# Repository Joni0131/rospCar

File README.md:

- [rospCar](#rospcar)
- [Work progression](#work-progression)
  - [1. Old System](#1-old-system)
  - [2. Planning](#2-planning)
  - [3. ESP-32](#3-esp-32)
  - [4. Brain](#4-brain)
- [Resume](#resume)

# rospCar

This repository contains the whole redevelopment of an old RC car.

To change the control system to an esp32 and a ROS communication with the computer to potentially implement a SLAM algorithm.

# Work progression

I structured my work in the following four steps. Those are shortly discussed on this page for more detailed information on each step please correspond to each designated page.

## 1. [Old System](oldSystem/)

The first step of the redevelopment process consists of understanding and checking the currently used electronics. As well as their functionality.

## 2. [Planning](upgradePlan/)

In the second phase, I chose the requirements for the new car, ordered parts that fulfill those requirements as well as designed the new circuit diagram.

## 3. [ESP-32](esp/)

The third step is considered the heart of the hardware development process. Here I define the functional requirements for the esp-32 and implement those decently.

## 4. [Brain](brain/)

Last but not least I design the other side of the communication and control algorithm for this project on the computer. The computer software is calculating the movements of the car and is using the sensor data to do this. Furthermore, it will be using a SLAM algorithm to map the whole area and it will be possible to go to certain locations easily.

# Resume

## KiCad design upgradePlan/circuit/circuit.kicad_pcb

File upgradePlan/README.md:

- [2. Planning](#2-planning)
  - [2.1 Funktional requiremnets](#21-funktional-requiremnets)
  - [2.2 Reqiered Hardware](#22-reqiered-hardware)
  - [2.3 Circuit Diagram](#23-circuit-diagram)

# 2. Planning
In this folder, I am planning the improvements for the rospCar inclusive of the new circuit diagram.

## 2.1 Funktional requiremnets

The rospCar has to fulfill multiple requirements.
 - steering
 - impulsion
 - controlling
 - voltage regulation
 - communication with another device via WIFI
 - environment tracking
 - front and back lights
 - similar appearance to the old system
 - speed information
## 2.2 Required Hardware
To fulfill those requirements multiple hardware components are necessary.
- For steering, use a [SG90 Micro Servomotor](http://www.ee.ic.ac.uk/pcheung/teaching/DE1_EE/stores/sg90_datasheet.pdf). With such a motor the steering accuracy can be improved.
- The impulsion motor is defective so a new motor has to be inserted. For this, I bought a new [motor](https://www.luedeke-elektronic.de/DC-Kleinmotor-2-5V-6V-DC-210mA-14-500U-Min-MOT2.html) of a similar size.
- As a motor controllers, I am using two L9110H.
- To regulate the voltage going to the motor I am using the voltage regulator LM317T.
- Because the car should be able to communicate with another device using WIFI, I need a WIFI module. However, I want to use ROS2 as the communication system between those devices. This is a problem because on most really small microcontrollers it is not supported. I choose [micro-ROS](https://micro.ros.org/) which is capable of running on such small chips. But support for microcontrollers to communicate with WIFI is limited so I choose the [ESP-32](https://www.espressif.com/en/products/socs/esp32) as my main microcontroller.
- For environmental tracking there are multiple options:
  - <ins>Ultrasonic sensor:</ins> This is a cheap method to detect objects and their distance. However, I am not sure how accurate this tracking is gonna be and so it is a bad option for a SLAM algorithm. But I still wanna try it I bought the HC-SR04 as an ultrasonic sensor.
  - <ins>ToF sensor:</ins> Because ToF sensors can detect distances quite accurately it is a good option for a SLAM algorithm. However, it has to be kept in mind that transparent objects could not be detected. Another disadvantage of those sensors is that it only detects objects at the same height as the sensor. Even though I decided I want to use such a sensor. So I bought the VL53L0/1XV2 and will try to use those.
  - <ins>Camera:</ins> A camera would be good to get colors of the surroundings as well as a huge part of it. Because of the lens. I am currently not sure if I will be using a camera however if I want to add one I will be adding the 0V2640 camera to the ESP-32.
- The lights of the old system can still be used.
- The speed of the rospCar is detected with an accelerometer ITG/MPU6050/GY-521.
- For the electric circuit, I need a few resistors, capacitors and wires.
## 2.3 Circuit Diagram
### 2.3.1 V0.1
To test that the baisic functionality of driving and steering is working my circuit design does not include any environment sensors only the acceleration sensor, the motors and the LED's.

#### 2.3.1.1 Learnings
When building and implementing the first functionalitis I learned that I can't use the Pin's 34-39 for output signals. Also all Pins that have the ACD2 connected can't be used because of the needed Wifi. Those the relevant pins have to be rearanged.

Also the LED's can't be connected in this way so that has to be changed as well.

For a third optimization it might be neccessary to increase the voltage for the impulsion motor drive. However, it has to be keept in mind that that voltage is also powering the L293D those it should not be overvoltaged. It can also be considered to exchange the LM317 for another trasformer that is cappable of higher current.

### 2.3.2 V0.2
To fully implement and to consider all hardware limitations I am now adding a Ultarsonic and Time-of-Flight sensor to the system including some of the learnings from before.

#### 2.3.2.1 Learning
The motor is still not starting without help and the motor will get power in the boot process because the motor driver is enabled when it is booting.

### 2.3.3 V0.3
To get the motor starting I separated the Power circuit for the L293D and the motor power circuit. I also added a inverter based on a transistor for the enable signal for the motor driver because the esp pin will always be in the HIGH state in the boot process.

## 2.4 PCB design

After a few schematic iterations I started designing the PCB.

### 2.4.1 V0.3
To design the PCB I added footprints to all the schematic symbols in KiCad and than placed it on a board. I then used FreeRouting to do a first automated routing for the PCB. I decided that the width of each lane is with 1 mm more than enough to handle the load of the system.

Because this is my first designed board and also the first prototype I did not optimize the length of each line and those reduced latency. In this setup it is more than enough like that and can be done in the future.

Here a not complete 3D image of the planed PCB.

And here the first soldered PCB.

#### 2.4.1.1 Learningdd

The pcb is still way to big. Those the next iteration needs to be smaller. Another learning is that the motor controller and the 3 voltage regulators are getting quite hot after a short test. Those I will add some kind of heat sink to them.

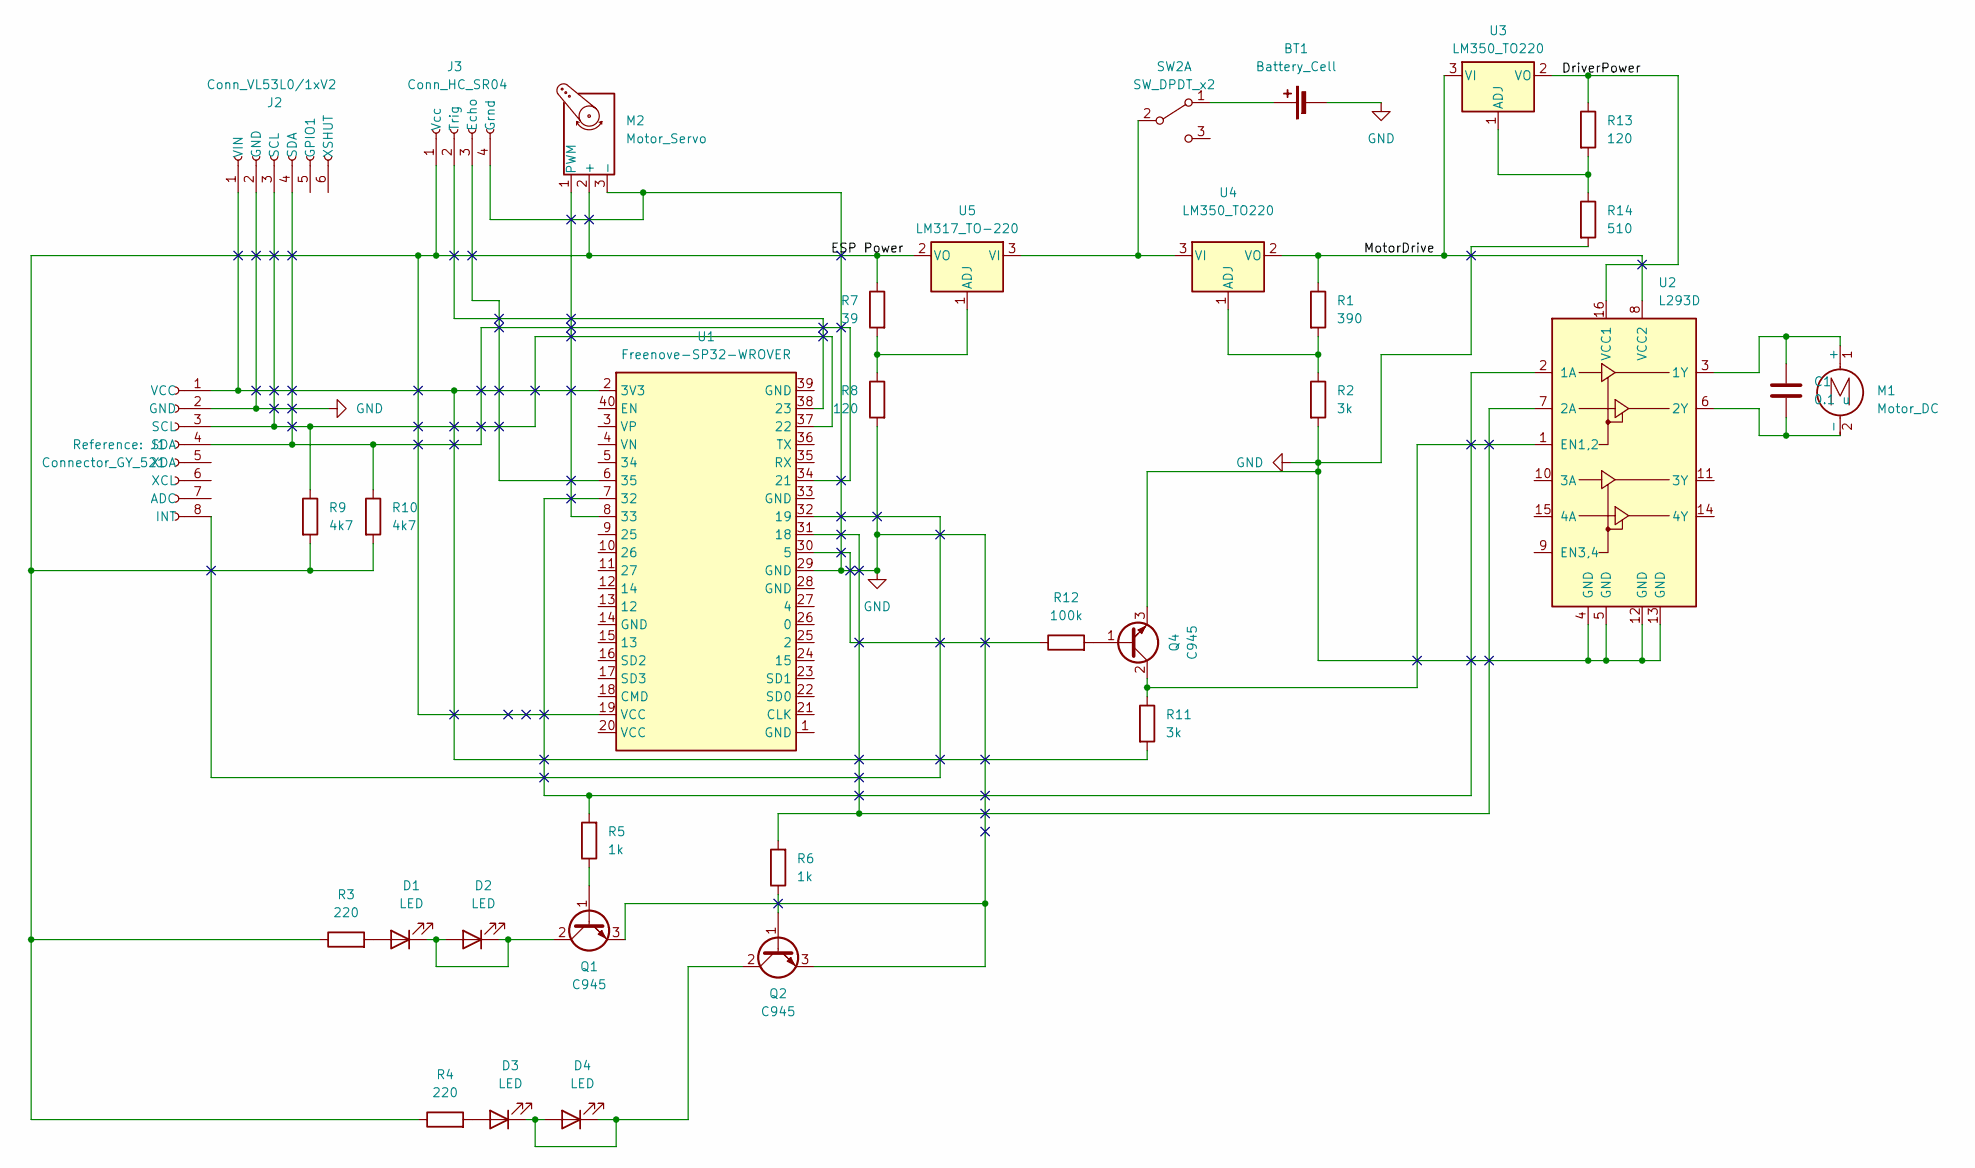
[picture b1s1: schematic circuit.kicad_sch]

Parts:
BT1: Battery_Cell; AMASS_XT60-M_1x02_P7.20mm_Vertical
C1: 0.1 u
D1, D3: LED; PhoenixContact_SPT_2.5_2-V-5.0-EX_1x02_P5.0mm_Vertical
D2, D4: LED
J1: Connector_GY_521; GY-521
J2: Conn_VL53L0/1xV2; PinHeader_1x06_P2.54mm_Horizontal
J3: Conn_HC_SR04; PinHeader_1x04_P2.54mm_Horizontal
M1: Motor_DC; PhoenixContact_SPT_2.5_2-V-5.0-EX_1x02_P5.0mm_Vertical
M2: Motor_Servo; PinHeader_1x03_P2.54mm_Horizontal
Q1, Q2, Q4: C945; TO-92
R1: 390; R_Axial_DIN0207_L6.3mm_D2.5mm_P15.24mm_Horizontal
R2, R11: 3k; R_Axial_DIN0207_L6.3mm_D2.5mm_P15.24mm_Horizontal
R3, R4: 220; R_Axial_DIN0207_L6.3mm_D2.5mm_P15.24mm_Horizontal
R5, R6: 1k; R_Axial_DIN0207_L6.3mm_D2.5mm_P15.24mm_Horizontal
R7: 39; R_Axial_DIN0207_L6.3mm_D2.5mm_P15.24mm_Horizontal
R8, R13: 120; R_Axial_DIN0207_L6.3mm_D2.5mm_P15.24mm_Horizontal
R9, R10: 4k7; R_Axial_DIN0207_L6.3mm_D2.5mm_P15.24mm_Horizontal
R12: 100k; R_Axial_DIN0207_L6.3mm_D2.5mm_P15.24mm_Horizontal
R14: 510; R_Axial_DIN0207_L6.3mm_D2.5mm_P15.24mm_Horizontal
SW2: SW_DPDT_x2; SW_Slide_1P2T_CK_OS102011MS2Q
U1: Freenove-SP32-WROVER; MyESPConnector
U2: L293D; DIP-16_W7.62mm
U3, U4: LM350_TO220; TO-220-3_Horizontal_TabDown
U5: LM317_TO-220; TO-220-3_Horizontal_TabDown

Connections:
/DriverPower: R13.1, U2.16 (VCC1), U3.2 (VO)
/ESP Power: J3.1 (Vcc), M2.2 (+), R3.1, R4.1, R7.1, R9.2, R10.2, U1.19 (VCC), U5.2 (VO)
/MotorDrive: R1.1, U2.8 (VCC2), U3.3 (VI), U4.2 (VO)
GND: BT1.2 (-), J1.2 (GND), J2.2 (GND), J3.4 (Grnd), M2.3 (-), Q1.3 (E), Q2.3 (E), Q4.3 (E), R2.2, R8.2, R14.2, U1.29 (GND), U2.4 (GND), U2.5 (GND), U2.12 (GND), U2.13 (GND)
unnamed: BT1.1 (+), SW2.1 (A)
unnamed: D1.2 (A), R3.2
unnamed: D1.1 (K), D2.1 (K), D2.2 (A), Q1.2 (C)
unnamed: D3.2 (A), R4.2
unnamed: D3.1 (K), D4.1 (K), D4.2 (A), Q2.2 (C)
unnamed: J1.8 (INT), U1.32 (19)
unnamed: J1.3 (SCL), J2.3 (SCL), R9.1, U1.37 (22)
unnamed: J1.4 (SDA), J2.4 (SDA), R10.1, U1.34 (21)
unnamed: J1.1 (VCC), J2.1 (VIN), R11.2, U1.2 (3V3)
unnamed: J3.3 (Echo), U1.6 (35)
unnamed: J3.2 (Trig), U1.38 (23)
unnamed: C1.1, M1.1 (+), U2.3 (1Y)
unnamed: C1.2, M1.2 (-), U2.6 (2Y)
unnamed: M2.1 (PWM), U1.8 (33)
unnamed: Q1.1 (B), R5.1
unnamed: Q2.1 (B), R6.1
unnamed: Q4.1 (B), R12.2
unnamed: Q4.2 (C), R11.1, U2.1 (EN1,2)
unnamed: SW2.2 (B), U4.3 (VI), U5.3 (VI)
unnamed: R12.1, U1.30 (5)
unnamed: R6.2, U1.31 (18), U2.7 (2A)
unnamed: R5.2, U1.7 (32), U2.2 (1A)
unnamed: R13.2, R14.1, U3.1 (ADJ)
unnamed: R1.2, R2.1, U4.1 (ADJ)
unnamed: R7.2, R8.1, U5.1 (ADJ)

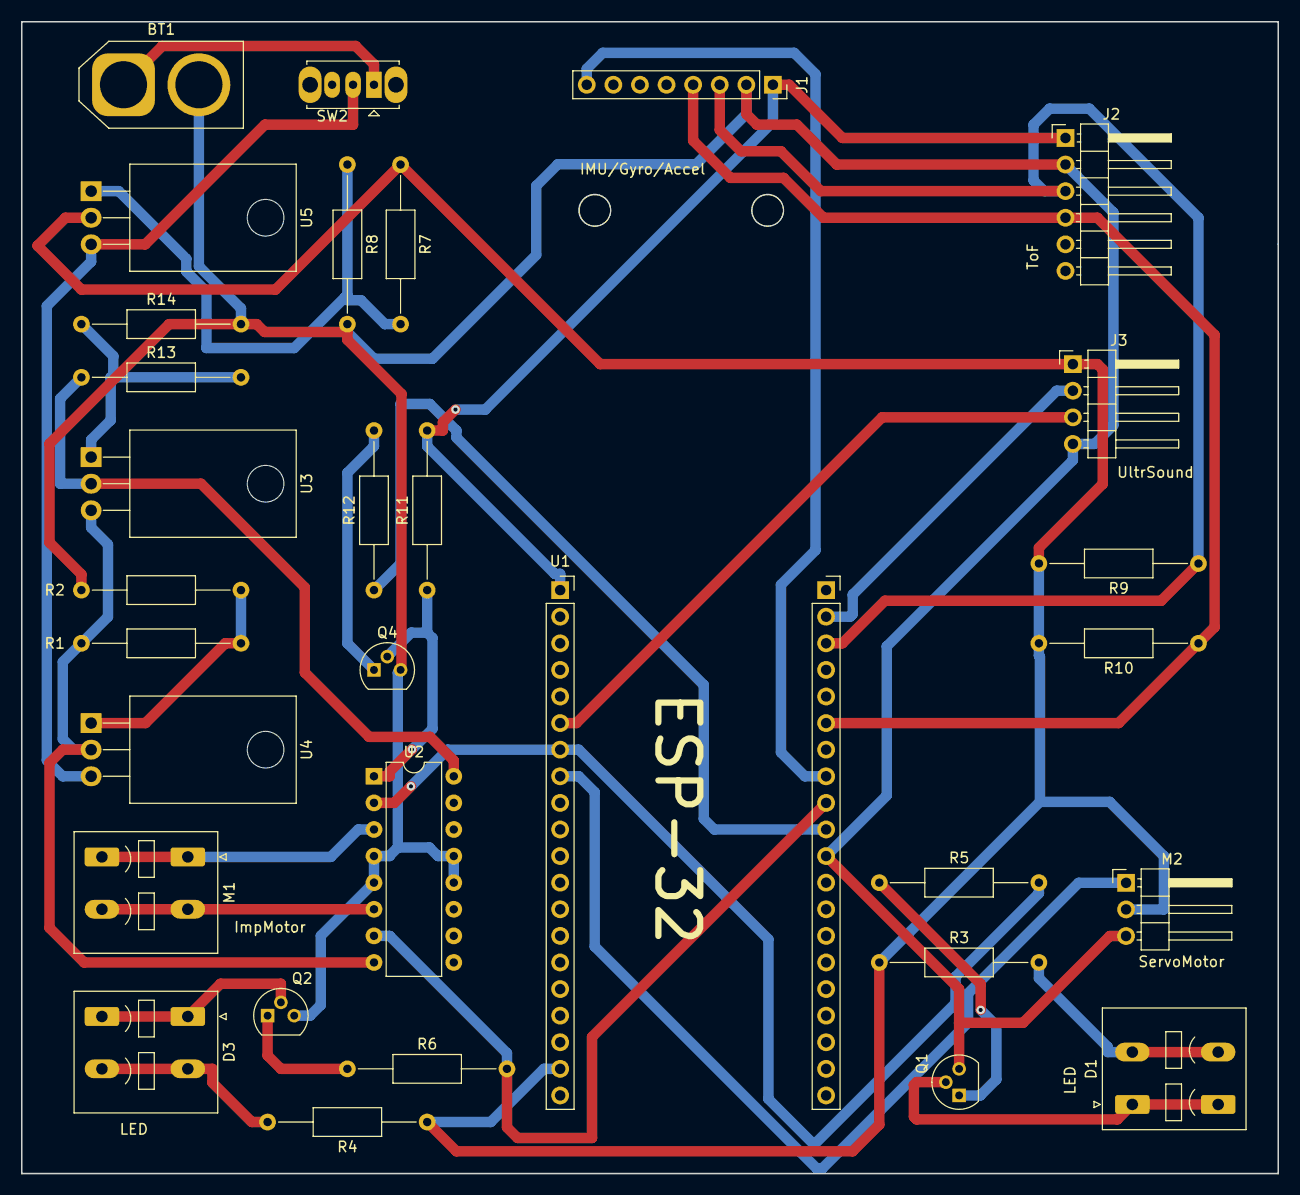
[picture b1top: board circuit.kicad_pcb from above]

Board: 2 copper layers, 120.0 x 110.0 mm, 31 parts (0 on the bottom side), 29 nets.

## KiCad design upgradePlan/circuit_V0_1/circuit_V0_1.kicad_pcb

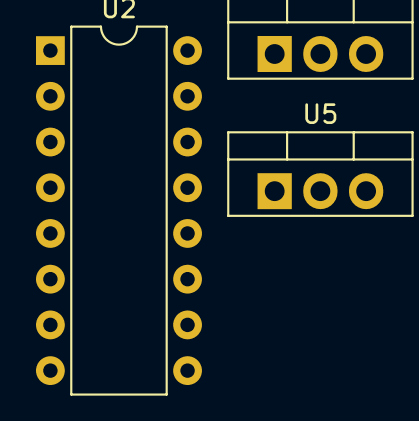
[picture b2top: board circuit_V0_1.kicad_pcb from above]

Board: 2 copper layers, 3 parts (0 on the bottom side), 2 nets, no tracks yet.

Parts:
U2: L293D; DIP-16_W7.62mm
U3, U5: LM317_TO-220; TO-220-3_Vertical

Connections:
/Drive Motor: U2.8 (VCC2), U2.16 (VCC1), U3.2 (VO)
unnamed: U3.3 (VI), U5.3 (VI)

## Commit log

2023-02-05 Create t
2023-02-06 created base file system
2023-02-07 working on old circuit diagram
2023-02-07 Add pictures of current electronics
    Here the pictures of the front and back of the pcb as well as the whole system
2023-02-10 working on Documentation setup and circuit diagram
2023-02-10 update gitignore
2023-02-10 change links in read me main
2023-02-12 Update the Main Read me and rename the pictures
2023-02-12 write old system read me and documentation
2023-02-13 update plan readme, fix gitignore to ignore the backups of the kicad project
2023-02-13 Working on the circuit design
2023-02-14 motor ciurcuit in kicad partial in picture
2023-07-12 Update README.md
    Updated motor driver.
2023-07-12 Update README.md
    Fixed wording
2023-10-28 circuit V0.1
2023-10-28 Added first requirements
2023-10-31 Changed name of the KiCadProject
2023-10-31 Default Wifi settings
2023-10-31 added the wifidefinitions to the gitignore
2023-10-31 added new git ignore
2023-10-31 added the wifi template
2023-11-01 FirstversionPoCof communication between ESP and PC
2023-11-01 Changed the circuit and added struct for custom messages
2023-11-02 Added new Messages for all the currently planned modules
2023-11-02 refactored the Subcriber and Publisher files So now a arbitray new element can be added
2023-11-02 created the publisher for the accelerometer created the setup for the mpu6050
2023-11-02 committed to much
2023-11-03 remoddeled the message for the accelerometer the accelerometer is now publishing it's results
2023-11-03 Added the steering servo tuning of max parameter and init based on current value missing
2023-11-05 made sure steering motor is not breaking / going in a not allowed angle added first guess of motor movement range
2023-11-05 implemented the impulsion functionality
2023-11-05 increased steering range aded impulsion motor in a working setup added the kicad autosave to the gitignore
2023-11-05 Added the HC_SR04 and the tof sensor to the schematic added the recommended changes Update the read me add datasheet for hc-sr04
2023-11-05 added the skeleton for the ultrasound and tof sensor MISSING Functionality
2023-11-08 Added resistor to I2C bus added setup and reading for ultrasound and tof sensor increased the max number of pub ERROR in Timer creation of the UltraSoundSensor when all others are initilized
2023-11-10 increased sensing distance of the ultra sound sensor if readings are off the voltage is to low
2023-11-15 Fixed the issue with a5th publoisher by combining all env sensor data in one topic
2023-11-15 fixed the loop speed so the pub and sub are working also added calibration skelleton for the accelerometer
2023-11-17 added new inti parameters to the accelerometer and commented the default precision of the senso
2023-12-03 increased voltage for the motor added a signal inverter for the enable pin. Added that into the code as well
2023-12-05 added footprints to schematic and board edge
2023-12-06 added layout of footprints
2023-12-06 added front routing with auto completed back
2023-12-07 Finished pcb Updated readme Generated Gerber files
2023-12-07 small layout fix in readme
2024-01-28 newest version of the printed pcb including updated read me for the planning
2024-05-27 FIxed wrong copnnection in pcb and updated code correspondingly. Switch pin 31 and 30.
2024-10-28 [WIP] Adding service to call the configuration of the accelerometer
2024-10-28 [WIP] Fixed a typo in the nameing
